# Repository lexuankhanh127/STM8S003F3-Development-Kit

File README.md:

# STM8S003F3-DEVELOPMENT-KIT

## 1. PCB

## 2. Crystal Speed Test and Code Upload ( Watch on YouTube )

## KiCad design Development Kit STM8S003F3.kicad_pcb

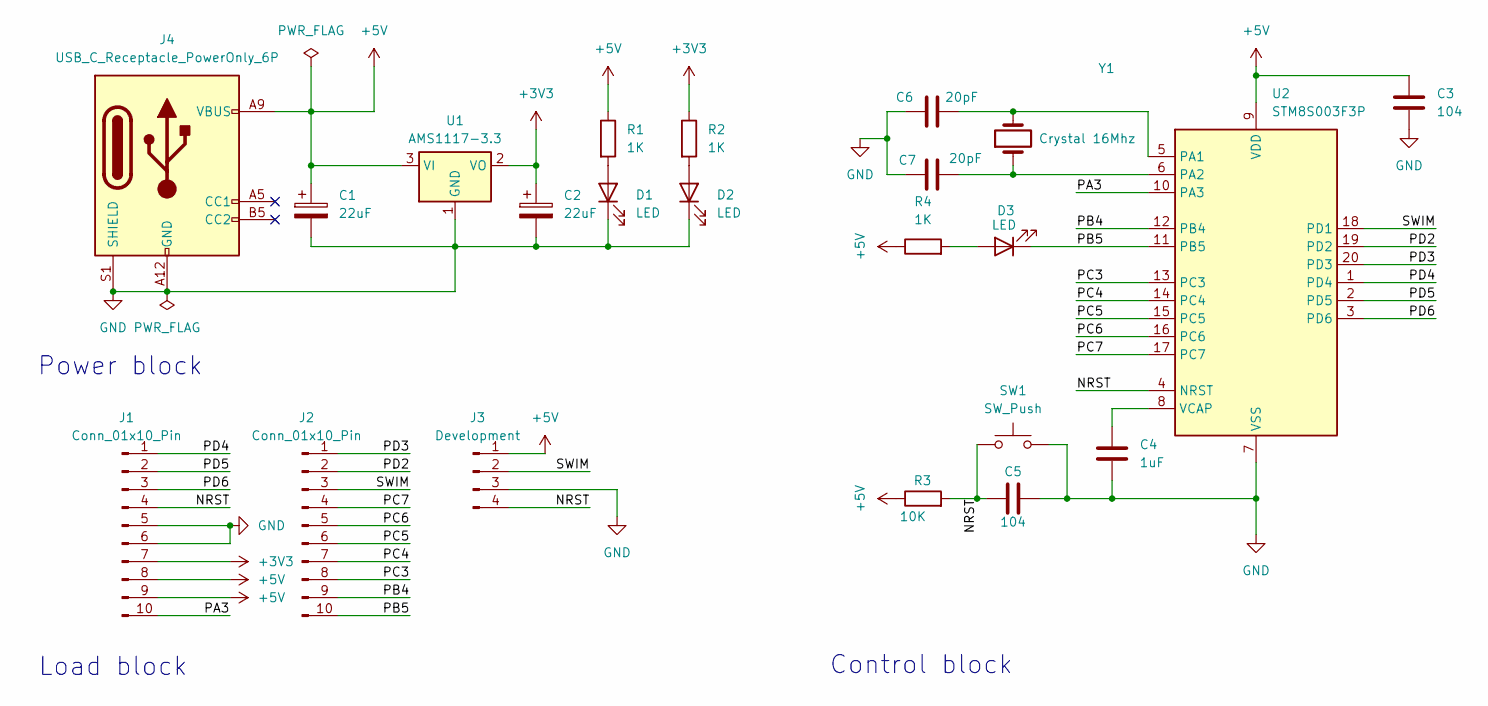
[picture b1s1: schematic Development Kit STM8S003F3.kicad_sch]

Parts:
C1, C2: 22uF; CP_Elec_4x5.4
C3, C5: 104; C_0805_2012Metric_Pad1.18x1.45mm_HandSolder
C4: 1uF; C_0805_2012Metric_Pad1.18x1.45mm_HandSolder
C6, C7: 20pF; C_0805_2012Metric_Pad1.18x1.45mm_HandSolder
D1, D2, D3: LED; LED_0805_2012Metric_Pad1.15x1.40mm_HandSolder
J1, J2: Conn_01x10_Pin; PinHeader_1x10_P2.54mm_Vertical
J3: Development; PinHeader_1x04_P2.54mm_Vertical
J4: USB_C_Receptacle_PowerOnly_6P; USB_C_Receptacle_HRO_TYPE-C-31-M-17
R1, R2, R4: 1K; R_0805_2012Metric_Pad1.20x1.40mm_HandSolder
R3: 10K; R_0805_2012Metric_Pad1.20x1.40mm_HandSolder
SW1: SW_Push; SW_Push_1P1T_NO_E-Switch_TL3301NxxxxxG
U1: AMS1117-3.3; SOT-223-3_TabPin2
U2: STM8S003F3P; TSSOP-20_4.4x6.5mm_P0.65mm
Y1: Crystal 16Mhz; Crystal_SMD_HC49-SD_HandSoldering

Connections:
+3V3: C2.1, J1.7, R2.1, U1.2 (VO)
+5V: C1.1, C3.1, J1.8, J1.9, J3.1, J4.A9 (VBUS), J4.B9 (VBUS), R1.1, R3.1, R4.1, U1.3 (VI), U2.9 (VDD)
/NRST: C5.1, J1.4, J3.4, R3.2, SW1.1, U2.4 (NRST)
/PA3: J1.10, U2.10 (PA3)
/PB4: J2.9, U2.12 (PB4)
/PB5: D3.1 (K), J2.10, U2.11 (PB5)
/PC3: J2.8, U2.13 (PC3)
/PC4: J2.7, U2.14 (PC4)
/PC5: J2.6, U2.15 (PC5)
/PC6: J2.5, U2.16 (PC6)
/PC7: J2.4, U2.17 (PC7)
/PD2: J2.2, U2.19 (PD2)
/PD3: J2.1, U2.20 (PD3)
/PD4: J1.1, U2.1 (PD4)
/PD5: J1.2, U2.2 (PD5)
/PD6: J1.3, U2.3 (PD6)
/SWIM: J2.3, J3.2, U2.18 (PD1)
GND: C1.2, C2.2, C3.2, C4.2, C5.2, C6.1, C7.2, D1.1 (K), D2.1 (K), J1.5, J1.6, J3.3, J4.A12 (GND), J4.B12 (GND), J4.S1 (SHIELD), SW1.2, U1.1 (GND), U2.7 (VSS)
unnamed: D1.2 (A), R1.2
unnamed: D2.2 (A), R2.2
unnamed: D3.2 (A), R4.2
unnamed: C6.2, U2.5 (PA1), Y1.2
unnamed: C7.1, U2.6 (PA2), Y1.1
unnamed: C4.1, U2.8 (VCAP)

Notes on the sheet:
Control block
Power block
Load block

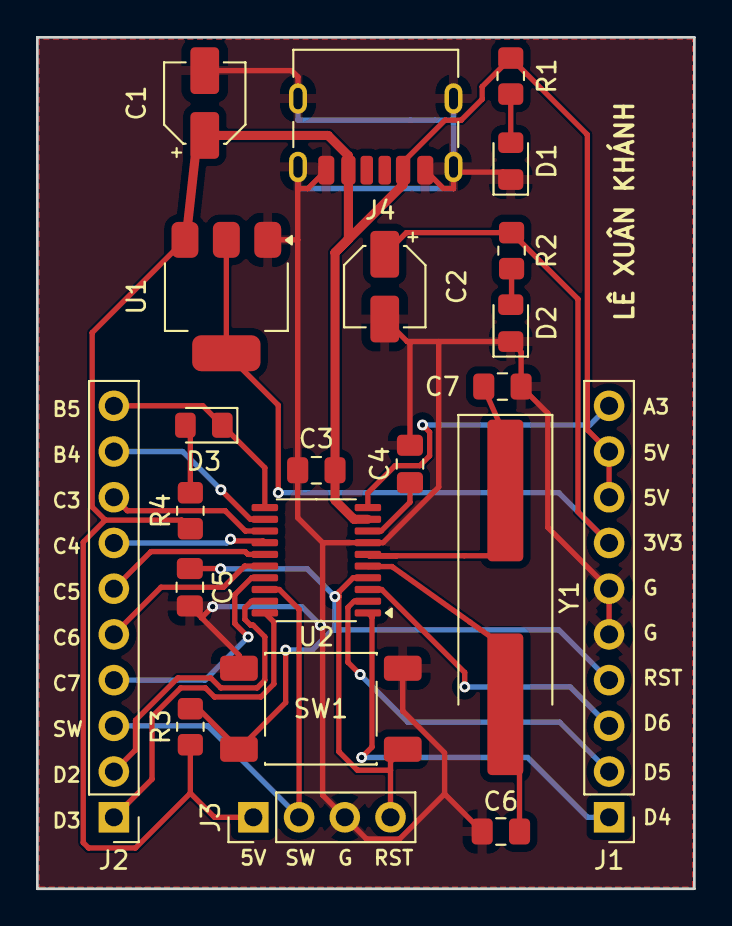
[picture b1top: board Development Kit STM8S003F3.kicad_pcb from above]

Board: 2 copper layers, 36.5 x 47.3 mm, 22 parts (0 on the bottom side), 24 nets.
